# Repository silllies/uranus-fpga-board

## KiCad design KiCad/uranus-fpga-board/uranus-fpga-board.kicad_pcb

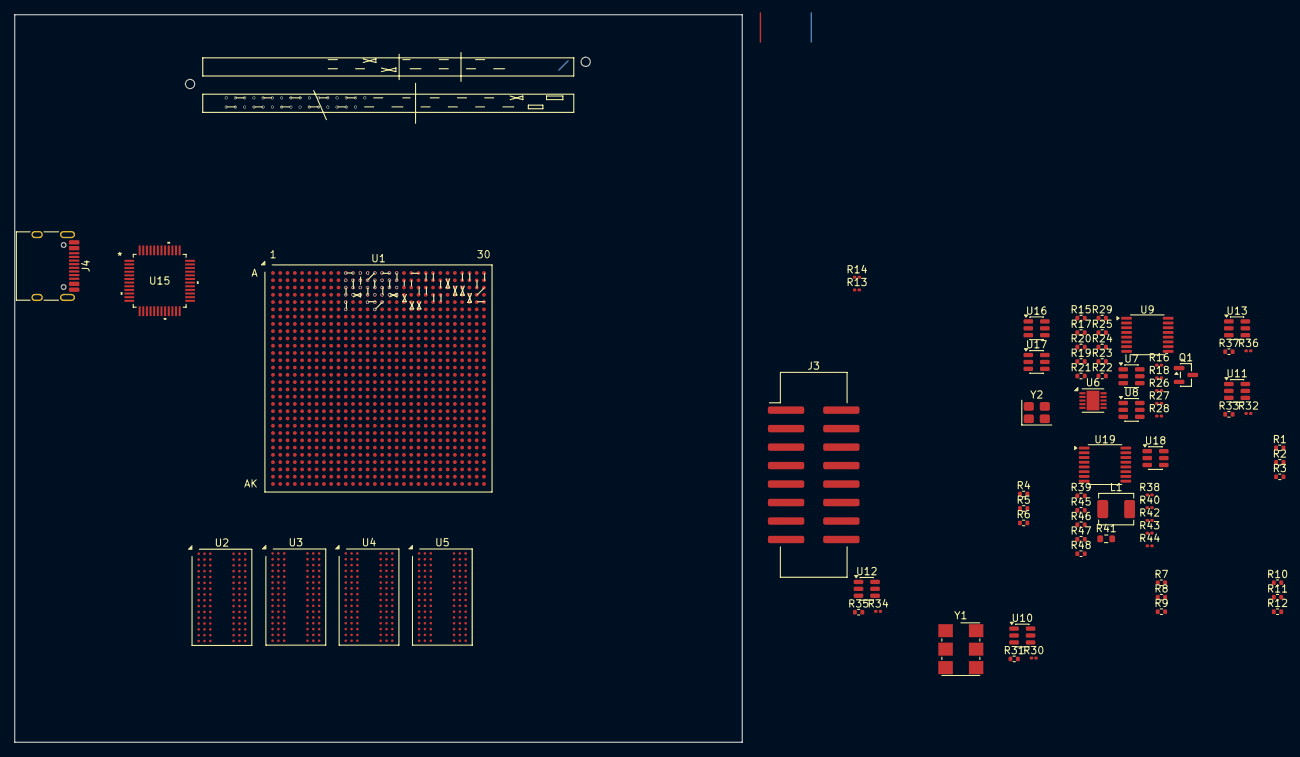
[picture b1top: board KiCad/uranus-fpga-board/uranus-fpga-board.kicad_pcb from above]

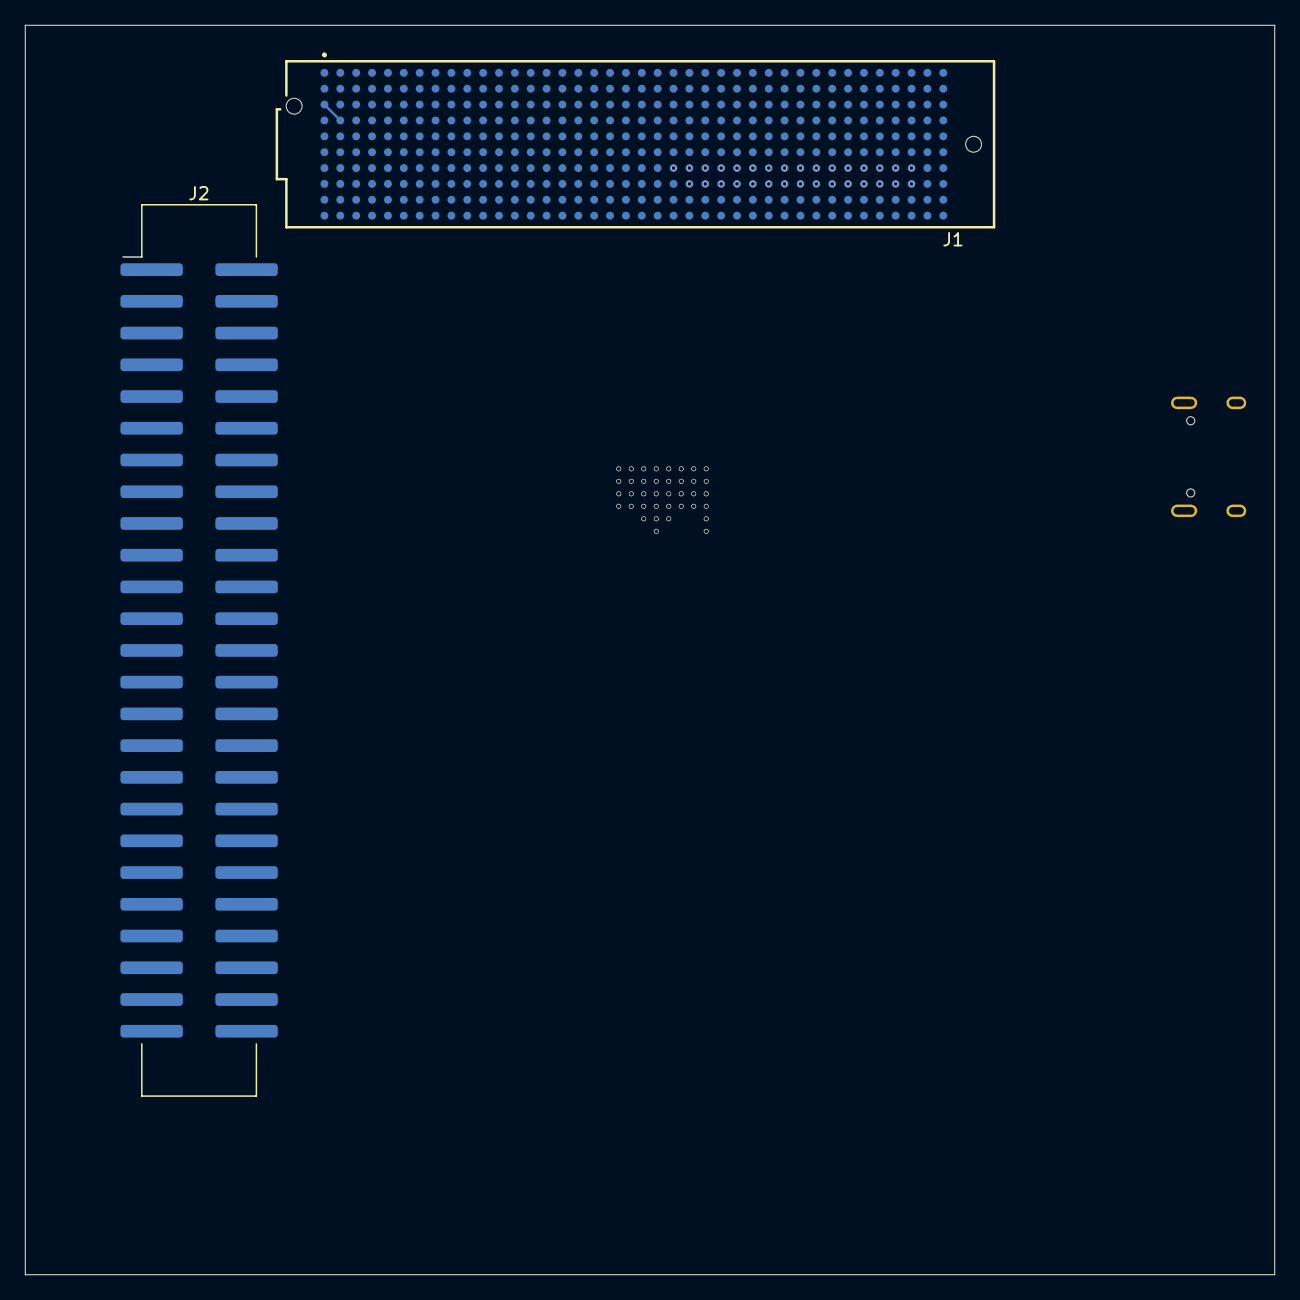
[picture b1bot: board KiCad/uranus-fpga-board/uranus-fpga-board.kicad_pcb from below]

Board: 8 copper layers, 100.0 x 100.0 mm, 74 parts (2 on the bottom side), 244 nets.

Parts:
J1: ASP-134486-01; SAMTEC_ASP-134486-01
J2: 1040100018; IDC-Header_2x25_P2.54mm_Vertical_SMD
J3: IDC 2x8; IDC-Header_2x08_P2.54mm_Vertical_SMD
J4: TYPE-C-31-M-12; USB_C_Receptacle_HRO_TYPE-C-31-M-12
L1: 2.2 μH; L_Chilisin_BMRA00040415
Q1: 2N7002; SOT-23
R1, R2, R4, R5, R7, R8, R10, R11: 1 kΩ; R_0402_1005Metric
R3, R6, R9, R12: 240 Ω; R_0402_1005Metric
R13, R14, R16, R38: 10 kΩ; R_0201_0603Metric
R15: 1.8 kΩ; R_0402_1005Metric
R17: 200 kΩ; R_0402_1005Metric
R18: 7.5 kΩ; R_0201_0603Metric
R19, R20, R22: 57.6 kΩ; R_0402_1005Metric
R21: 232 kΩ; R_0402_1005Metric
R23: 41.2 kΩ; R_0402_1005Metric
R24: 27.4 kΩ; R_0402_1005Metric
R25: 21.5 kΩ; R_0402_1005Metric
R26, R27, R28, R42, R43, R44: 200 kΩ; R_0201_0603Metric
R29: 15.8 kΩ; R_0402_1005Metric
R30, R32, R34, R36: 499 Ω; R_0201_0603Metric
R31, R33, R35, R37: 7.68 kΩ; R_0402_1005Metric
R39: 4.7 kΩ; R_0402_1005Metric
R40: 30 kΩ; R_0201_0603Metric
R41: 8.98 kΩ; R_0603_1608Metric
R45: 13 kΩ; R_0402_1005Metric
R46: 22.1 kΩ; R_0402_1005Metric
R47: 30.9 kΩ; R_0402_1005Metric
R48: 52.3 kΩ; R_0402_1005Metric
U1: XC7K325T-3FFG900E; Xilinx_FFG900_FFG901
U2, U3, U4, U5: NT5CB64M16GP-FL; FBGA-96_8x13mm_Layout9x16_P0.8mm
U6: SY6874DBC; DFN-10-1EP_3x3mm_P0.5mm_EP1.75x2.7mm
U7: TPS2553DBVR; SOT-23-6
U8: SY6288F1ABC; SOT-23-6
U9, U19: TMUX1108; TSSOP-16_4.4x5mm_P0.65mm
U10, U11, U12, U13: TLV6700DDCR; SOT-23-6
U15: FT232HL-REEL; LQFP48_FT232HL_FTD
U16: 93LC56BT; SOT-23-6
U17: USBLC6-2SC6; SOT-23-6
U18: TPS564201DDCR; SOT-23-6
Y1: SX7DF200.000B20F30DNN; Oscillator_SMD_IDT_JU6-6_7.0x5.0mm_P2.54mm
Y2: 3225-12-20-10-10/4B; Crystal_SMD_3225-4Pin_3.2x2.5mm

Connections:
+1V0: U1.M11 (VCCINT), U1.M13 (VCCINT), U1.M15 (VCCINT), U1.M17 (VCCINT), U1.N10 (VCCINT), U1.N12 (VCCINT), U1.N14 (VCCINT), U1.N16 (VCCBRAM), U1.N18 (VCCINT), U1.P11 (VCCINT), U1.P17 (VCCINT), U1.R10 (VCCINT), U1.R12 (VCCINT), U1.R16 (VCCBRAM), U1.R18 (VCCINT), U1.T11 (VCCINT), U1.T17 (VCCINT), U1.U10 (VCCINT), U1.U12 (VCCINT), U1.U16 (VCCBRAM), U1.U18 (VCCINT), U1.V17 (VCCINT), U1.W16 (VCCBRAM), U1.W18 (VCCINT)
+1V5: R1.1, R4.1, R7.1, R10.1, U1.AA9 (VCCO_33), U1.AA19 (VCCO_32), U1.AB16 (VCCO_32), U1.AC3 (VCCO_34), U1.AC13 (VCCO_33), U1.AD10 (VCCO_33), U1.AE7 (VCCO_34), U1.AE17 (VCCO_32), U1.AF4 (VCCO_34), U1.AF14 (VCCO_32), U1.AG1 (VCCO_34), U1.AG11 (VCCO_33), U1.AH8 (VCCO_34), U1.AH18 (VCCO_32), U1.AJ5 (VCCO_34), U1.AJ15 (VCCO_32), U1.AK2 (VCCO_34), U1.AK12 (VCCO_33), U1.Y12 (VCCO_33), U2.A1 (VDDQ), U2.A8 (VDDQ), U2.B2 (VDD), U2.C1 (VDDQ), U2.C9 (VDDQ), U2.D2 (VDDQ), U2.D9 (VDD), U2.E9 (VDDQ), U2.F1 (VDDQ), U2.G7 (VDD), U2.H2 (VDDQ), U2.H9 (VDDQ), U2.K2 (VDD), U2.K8 (VDD), U2.N1 (VDD), U2.N9 (VDD), U2.R1 (VDD), U2.R9 (VDD), U3.A1 (VDDQ), U3.A8 (VDDQ), U3.B2 (VDD), U3.C1 (VDDQ), U3.C9 (VDDQ), U3.D2 (VDDQ), U3.D9 (VDD), U3.E9 (VDDQ), U3.F1 (VDDQ), U3.G7 (VDD), U3.H2 (VDDQ), U3.H9 (VDDQ), U3.K2 (VDD), U3.K8 (VDD), U3.N1 (VDD), U3.N9 (VDD), U3.R1 (VDD), U3.R9 (VDD), U4.A1 (VDDQ), U4.A8 (VDDQ), U4.B2 (VDD), U4.C1 (VDDQ), U4.C9 (VDDQ), U4.D2 (VDDQ), U4.D9 (VDD), U4.E9 (VDDQ), U4.F1 (VDDQ), U4.G7 (VDD), U4.H2 (VDDQ), U4.H9 (VDDQ), U4.K2 (VDD), U4.K8 (VDD), U4.N1 (VDD), U4.N9 (VDD), U4.R1 (VDD), U4.R9 (VDD), U5.A1 (VDDQ), U5.A8 (VDDQ), U5.B2 (VDD), U5.C1 (VDDQ), U5.C9 (VDDQ), U5.D2 (VDDQ), U5.D9 (VDD), U5.E9 (VDDQ), U5.F1 (VDDQ), U5.G7 (VDD), U5.H2 (VDDQ), U5.H9 (VDDQ), U5.K2 (VDD), U5.K8 (VDD), U5.N1 (VDD), U5.N9 (VDD), U5.R1 (VDD), U5.R9 (VDD)
+1V8: U1.P13 (VCCAUX), U1.P15 (VCCADC_0), U1.T13 (VCCAUX), U1.V13 (VCCAUX)
+2V0: U1.V11 (VCCAUX_IO_G0), U1.W10 (VCCAUX_IO_G0), U1.W12 (VCCAUX_IO_G0)
+3V3: J3.1 (VIN), R13.1, R16.1, U1.AB6 (VCCO_0), U1.J25 (VCCO_15), U1.K22 (VCCO_15), U1.L29 (VCCO_15), U1.M26 (VCCO_15), U1.N23 (VCCO_15), U1.P20 (VCCO_15), U1.T9 (VCCO_0), U7.1 (IN), U7.3 (EN), U8.6 (IN), U10.5 (VDD), U11.5 (VDD), U12.5 (VDD), U13.5 (VDD), Y1.6 (VDD)
+3V3AUX: J1.D32 (3P3VAUX), R19.2, U7.6 (OUT)
+3V3_P: J1.C39 (3P3V), J1.D36 (3P3V), J1.D38 (3P3V), J1.D40 (3P3V), R14.1, R20.2, U8.1 (OUT)
+5V0: U9.2 (EN), U9.13 (VDD), U19.2 (EN), U19.13 (VDD)
+12V0: J1.C35 (12P0V), J1.C37 (12P0V), U6.1 (IN), U18.3 (VIN)
+12V0_P: R21.2, U6.8 (OUT), U6.9 (VOUT), U6.10 (VOUT)
/FMC/CLK0_N: J1.H05 (CLK0_M2C_N), U1.B25 (IO_L12N_T1_MRCC_16)
/FMC/CLK0_P: J1.H04 (CLK0_M2C_P), U1.C25 (IO_L12P_T1_MRCC_16)
/FMC/CLK1_N: J1.G03 (CLK1_M2C_N), U1.D28 (IO_L14N_T2_SRCC_16)
/FMC/CLK1_P: J1.G02 (CLK1_M2C_P), U1.E28 (IO_L14P_T2_SRCC_16)
/FMC/DP0_C2M_N: J1.C03 (DP0_C2M_N), U1.B1 (MGTXTXN2_118)
/FMC/DP0_C2M_P: J1.C02 (DP0_C2M_P), U1.B2 (MGTXTXP2_118)
/FMC/DP0_M2C_N: J1.C07 (DP0_M2C_N), U1.B5 (MGTXRXN2_118)
/FMC/DP0_M2C_P: J1.C06 (DP0_M2C_P), U1.B6 (MGTXRXP2_118)
/FMC/GTXCLK0_N: J1.D05 (GBTCLK0_M2C_N), U1.C7 (MGTREFCLK0N_118)
/FMC/GTXCLK0_P: J1.D04 (GBTCLK0_M2C_P), U1.C8 (MGTREFCLK0P_118)
/FMC/LA00_CC_N: J1.G07 (LA00_CC_N), U1.C27 (IO_L13N_T2_MRCC_16)
/FMC/LA00_CC_P: J1.G06 (LA00_CC_P), U1.D27 (IO_L13P_T2_MRCC_16)
/FMC/LA01_N: J1.D09 (LA01_N), U1.E29 (IO_L18P_T2_16)
/FMC/LA01_P: J1.D08 (LA01_P), U1.E30 (IO_L18N_T2_16)
/FMC/LA02_N: J1.H08 (LA02_N), U1.D29 (IO_L16P_T2_16)
/FMC/LA02_P: J1.H07 (LA02_P), U1.C30 (IO_L16N_T2_16)
/FMC/LA03_N: J1.G10 (LA03_N), U1.A30 (IO_L17N_T2_16)
/FMC/LA03_P: J1.G09 (LA03_P), U1.B30 (IO_L17P_T2_16)
/FMC/LA04_N: J1.H11 (LA04_N), U1.B29 (IO_L15N_T2_DQS_16)
/FMC/LA04_P: J1.H10 (LA04_P), U1.C29 (IO_L15P_T2_DQS_16)
/FMC/LA05_N: J1.D12 (LA05_N), U1.D23 (IO_L2N_T0_16)
/FMC/LA05_P: J1.D11 (LA05_P), U1.E23 (IO_L2P_T0_16)
/FMC/LA06_N: J1.C11 (LA06_N), U1.D24 (IO_L4N_T0_16)
/FMC/LA06_P: J1.C10 (LA06_P), U1.E24 (IO_L4P_T0_16)
/FMC/LA07_N: J1.H14 (LA07_N), U1.A27 (IO_L7N_T1_16)
/FMC/LA07_P: J1.H13 (LA07_P), U1.B27 (IO_L7P_T1_16)
/FMC/LA08_N: J1.G13 (LA08_N), U1.A28 (IO_L9N_T1_DQS_16)
/FMC/LA08_P: J1.G12 (LA08_P), U1.B28 (IO_L9P_T1_DQS_16)
/FMC/LA09_N: J1.D15 (LA09_N), U1.C22 (IO_L10N_T1_17)
/FMC/LA09_P: J1.D14 (LA09_P), U1.D22 (IO_L10P_T1_17)
/FMC/LA10_N: J1.C15 (LA10_N), U1.C21 (IO_L8N_T1_17)
/FMC/LA10_P: J1.C14 (LA10_P), U1.D21 (IO_L8P_T1_17)
/FMC/LA11_N: J1.H17 (LA11_N), U1.A23 (IO_L1N_T0_16)
/FMC/LA11_P: J1.H16 (LA11_P), U1.B23 (IO_L1P_T0_16)
/FMC/LA12_N: J1.G16 (LA12_N), U1.B24 (IO_L8N_T1_16)
/FMC/LA12_P: J1.G15 (LA12_P), U1.C24 (IO_L8P_T1_16)
/FMC/LA13_N: J1.D18 (LA13_N), U1.D19 (IO_L14N_T2_SRCC_17)
/FMC/LA13_P: J1.D17 (LA13_P), U1.E19 (IO_L14P_T2_SRCC_17)
/FMC/LA14_N: J1.C19 (LA14_N), U1.C16 (IO_L15N_T2_DQS_17)
/FMC/LA14_P: J1.C18 (LA14_P), U1.D16 (IO_L15P_T2_DQS_17)
/FMC/LA15_N: J1.H20 (LA15_N), U1.A20 (IO_L21P_T3_DQS_17)
/FMC/LA15_P: J1.H19 (LA15_P), U1.A21 (IO_L21N_T3_DQS_17)
/FMC/LA16_N: J1.G19 (LA16_N), U1.A22 (IO_L23N_T3_17)
/FMC/LA16_P: J1.G18 (LA16_P), U1.B22 (IO_L23P_T3_17)
/FMC/LA17_CC_N: J1.D21 (LA17_CC_N), U1.D13 (IO_L13N_T2_MRCC_18)
/FMC/LA17_CC_P: J1.D20 (LA17_CC_P), U1.D12 (IO_L13P_T2_MRCC_18)
/FMC/LA18_CC_N: J1.C23 (LA18_CC_N), U1.D18 (IO_L13N_T2_MRCC_17)
/FMC/LA18_CC_P: J1.C22 (LA18_CC_P), U1.D17 (IO_L13P_T2_MRCC_17)
/FMC/LA19_N: J1.H23 (LA19_N), U1.C19 (IO_L24P_T3_17)
/FMC/LA19_P: J1.H22 (LA19_P), U1.B19 (IO_L24N_T3_17)
/FMC/LA20_N: J1.G22 (LA20_N), U1.C20 (IO_L19P_T3_17)
/FMC/LA20_P: J1.G21 (LA20_P), U1.B20 (IO_L19N_T3_VREF_17)
/FMC/LA21_N: J1.H26 (LA21_N), U1.C17 (IO_L17P_T2_17)
/FMC/LA21_P: J1.H25 (LA21_P), U1.B17 (IO_L17N_T2_17)
/FMC/LA22_N: J1.G25 (LA22_N), U1.B18 (IO_L22P_T3_17)
/FMC/LA22_P: J1.G24 (LA22_P), U1.A18 (IO_L22N_T3_17)
/FMC/LA23_N: J1.D24 (LA23_N), U1.F15 (IO_L19P_T3_18)
/FMC/LA23_P: J1.D23 (LA23_P), U1.E16 (IO_L19N_T3_VREF_18)
/FMC/LA24_N: J1.H29 (LA24_N), U1.C15 (IO_L23P_T3_18)
/FMC/LA24_P: J1.H28 (LA24_P), U1.B15 (IO_L23N_T3_18)
/FMC/LA25_N: J1.G28 (LA25_N), U1.A16 (IO_L20P_T3_17)
/FMC/LA25_P: J1.G27 (LA25_P), U1.A17 (IO_L20N_T3_17)
/FMC/LA26_N: J1.D27 (LA26_N), U1.E11 (IO_L16N_T2_18)
/FMC/LA26_P: J1.D26 (LA26_P), U1.F11 (IO_L16P_T2_18)
/FMC/LA27_N: J1.C27 (LA27_N), U1.E14 (IO_L20P_T3_18)
/FMC/LA27_P: J1.C26 (LA27_P), U1.E15 (IO_L20N_T3_18)
/FMC/LA28_N: J1.H32 (LA28_N), U1.D14 (IO_L21P_T3_DQS_18)
/FMC/LA28_P: J1.H31 (LA28_P), U1.C14 (IO_L21N_T3_DQS_18)
/FMC/LA29_N: J1.G31 (LA29_N), U1.B14 (IO_L24P_T3_18)
/FMC/LA29_P: J1.G30 (LA29_P), U1.A15 (IO_L24N_T3_18)
/FMC/LA30_N: J1.H35 (LA30_N), U1.A11 (IO_L17P_T2_18)
/FMC/LA30_P: J1.H34 (LA30_P), U1.A12 (IO_L17N_T2_18)
/FMC/LA31_N: J1.G34 (LA31_N), U1.B13 (IO_L22P_T3_18)
/FMC/LA31_P: J1.G33 (LA31_P), U1.A13 (IO_L22N_T3_18)
/FMC/LA32_N: J1.H38 (LA32_N), U1.D11 (IO_L18P_T2_18)
/FMC/LA32_P: J1.H37 (LA32_P), U1.C11 (IO_L18N_T2_18)
/FMC/LA33_N: J1.G37 (LA33_N), U1.C12 (IO_L15P_T2_DQS_18)
/FMC/LA33_P: J1.G36 (LA33_P), U1.B12 (IO_L15N_T2_DQS_18)
/FMC/PG: J1.D01 (PG_C2M), R14.2, U10.1 (OUTA), U10.6 (OUTB), U11.1 (OUTA), U11.6 (OUTB), U12.1 (OUTA), U12.6 (OUTB), U13.1 (OUTA), U13.6 (OUTB)
/FMC/Power Management/PRSNT: Q1.3 (D), R16.2, U6.2 (VIN), U6.3 (VIN), U6.7 (EN), U8.4 (EN)
/FMC/Power Management/Window Comparator +3V3AUX/IN: R19.1, R30.1, U10.3 (INA+)
/FMC/Power Management/Window Comparator +3V3_P/IN: R20.1, R34.1, U12.3 (INA+)
/FMC/Power Management/Window Comparator +12V0_P/IN: R21.1, R32.1, U11.3 (INA+)
/FMC/Power Management/Window Comparator VADJ/IN: R36.1, U9.8 (D), U13.3 (INA+)
/FMC/Power Management/~PRSNT: J1.H02 (~PRSNT_M2C), Q1.1 (G), R13.2
/FMC/REG_EN: R38.1, U18.5 (EN)
/FMC/SEL_A0: R26.2, R42.1, U9.1 (A0), U19.1 (A0)
/FMC/SEL_A1: R27.2, R43.1, U9.16 (A1), U19.16 (A1)
/FMC/SEL_A2: R28.2, R44.1, U9.15 (A2), U19.15 (A2)
/FPGA/CKE: U1.AJ9 (IO_L15P_T2_DQS_33), U2.K9 (CKE), U3.K9 (CKE), U4.K9 (CKE), U5.K9 (CKE)
/FPGA/H0.DM: U1.AF3 (IO_L7P_T1_34), U2.D3 (UDM)
/FPGA/H0.DQ0: U1.AF2 (IO_L7N_T1_34), U2.D7 (DQ8)
/FPGA/H0.DQ1: U1.AE1 (IO_L8P_T1_34), U2.C3 (DQ9)
/FPGA/H0.DQ2: U1.AF1 (IO_L8N_T1_34), U2.C8 (DQ10)
/FPGA/H0.DQ3: U1.AE4 (IO_L10P_T1_34), U2.C2 (DQ11)
/FPGA/H0.DQ4: U1.AE3 (IO_L10N_T1_34), U2.A7 (DQ12)
/FPGA/H0.DQ5: U1.AE5 (IO_L11P_T1_SRCC_34), U2.A2 (DQ13)
/FPGA/H0.DQ6: U1.AF5 (IO_L11N_T1_SRCC_34), U2.B8 (DQ14)
/FPGA/H0.DQ7: U1.AF6 (IO_L12P_T1_MRCC_34), U2.A3 (DQ15)
/FPGA/H0.DQS_N: U1.AG3 (IO_L9N_T1_DQS_34), U2.B7 (~UDQS)
/FPGA/H0.DQS_P: U1.AG4 (IO_L9P_T1_DQS_34), U2.C7 (UDQS)
/FPGA/H1.DM: U1.AF8 (IO_L19P_T3_34), U3.D3 (UDM)
/FPGA/H1.DQ0: U1.AF7 (IO_L20P_T3_34), U3.D7 (DQ8)
/FPGA/H1.DQ1: U1.AG7 (IO_L20N_T3_34), U3.C3 (DQ9)
/FPGA/H1.DQ2: U1.AJ6 (IO_L22P_T3_34), U3.C8 (DQ10)
/FPGA/H1.DQ3: U1.AK6 (IO_L22N_T3_34), U3.C2 (DQ11)
/FPGA/H1.DQ4: U1.AJ8 (IO_L23P_T3_34), U3.A7 (DQ12)
/FPGA/H1.DQ5: U1.AK8 (IO_L23N_T3_34), U3.A2 (DQ13)
/FPGA/H1.DQ6: U1.AK5 (IO_L24P_T3_34), U3.B8 (DQ14)
/FPGA/H1.DQ7: U1.AK4 (IO_L24N_T3_34), U3.A3 (DQ15)
/FPGA/H1.DQS_N: U1.AJ7 (IO_L21N_T3_DQS_34), U3.B7 (~UDQS)
/FPGA/H1.DQS_P: U1.AH7 (IO_L21P_T3_DQS_34), U3.C7 (UDQS)
/FPGA/H2.DM: U1.AJ19 (IO_L7P_T1_32), U4.D3 (UDM)
/FPGA/H2.DQ0: U1.AK19 (IO_L7N_T1_32), U4.D7 (DQ8)
/FPGA/H2.DQ1: U1.AG19 (IO_L8P_T1_32), U4.C3 (DQ9)
/FPGA/H2.DQ2: U1.AH19 (IO_L8N_T1_32), U4.C8 (DQ10)
/FPGA/H2.DQ3: U1.AD19 (IO_L10P_T1_32), U4.C2 (DQ11)
/FPGA/H2.DQ4: U1.AE19 (IO_L10N_T1_32), U4.A7 (DQ12)
/FPGA/H2.DQ5: U1.AF18 (IO_L11P_T1_SRCC_32), U4.A2 (DQ13)
/FPGA/H2.DQ6: U1.AG18 (IO_L11N_T1_SRCC_32), U4.B8 (DQ14)
/FPGA/H2.DQ7: U1.AF17 (IO_L12P_T1_MRCC_32), U4.A3 (DQ15)
/FPGA/H2.DQS_N: U1.AK18 (IO_L9N_T1_DQS_32), U4.B7 (~UDQS)
/FPGA/H2.DQS_P: U1.AJ18 (IO_L9P_T1_DQS_32), U4.C7 (UDQS)
/FPGA/H3.DM: U1.AA18 (IO_L16P_T2_32), U5.D3 (UDM)
/FPGA/H3.DQ0: U1.AD18 (IO_L13P_T2_MRCC_32), U5.D7 (DQ8)
/FPGA/H3.DQ1: U1.AE18 (IO_L13N_T2_MRCC_32), U5.C3 (DQ9)
/FPGA/H3.DQ2: U1.AD17 (IO_L14P_T2_SRCC_32), U5.C8 (DQ10)
/FPGA/H3.DQ3: U1.AD16 (IO_L14N_T2_SRCC_32), U5.C2 (DQ11)
/FPGA/H3.DQ4: U1.AB18 (IO_L16N_T2_32), U5.A7 (DQ12)
/FPGA/H3.DQ5: U1.AB19 (IO_L17P_T2_32), U5.A2 (DQ13)
/FPGA/H3.DQ6: U1.AC19 (IO_L17N_T2_32), U5.B8 (DQ14)
/FPGA/H3.DQ7: U1.AB17 (IO_L18P_T2_32), U5.A3 (DQ15)
/FPGA/H3.DQS_N: U1.Y18 (IO_L15N_T2_DQS_32), U5.B7 (~UDQS)
/FPGA/H3.DQS_P: U1.Y19 (IO_L15P_T2_DQS_32), U5.C7 (UDQS)
/FPGA/L0.DM: U1.AD4 (IO_L1P_T0_34), U2.E7 (LDM)
/FPGA/L0.DQ0: U1.AD3 (IO_L1N_T0_34), U2.E3 (DQ0)
/FPGA/L0.DQ1: U1.AC2 (IO_L2P_T0_34), U2.F7 (DQ1)
/FPGA/L0.DQ2: U1.AC1 (IO_L2N_T0_34), U2.F2 (DQ2)
/FPGA/L0.DQ3: U1.AC5 (IO_L4P_T0_34), U2.F8 (DQ3)
/FPGA/L0.DQ4: U1.AC4 (IO_L4N_T0_34), U2.H3 (DQ4)
/FPGA/L0.DQ5: U1.AD6 (IO_L5P_T0_34), U2.H8 (DQ5)
/FPGA/L0.DQ6: U1.AE6 (IO_L5N_T0_34), U2.G2 (DQ6)
/FPGA/L0.DQ7: U1.AC7 (IO_L6P_T0_34), U2.H7 (DQ7)
/FPGA/L0.DQS_N: U1.AD1 (IO_L3N_T0_DQS_34), U2.G3 (~LDQS)
/FPGA/L0.DQS_P: U1.AD2 (IO_L3P_T0_DQS_34), U2.F3 (LDQS)
/FPGA/L1.DM: U1.AH2 (IO_L16P_T2_34), U3.E7 (LDM)
/FPGA/L1.DQ0: U1.AH4 (IO_L13P_T2_MRCC_34), U3.E3 (DQ0)
/FPGA/L1.DQ1: U1.AJ4 (IO_L13N_T2_MRCC_34), U3.F7 (DQ1)
/FPGA/L1.DQ2: U1.AH6 (IO_L14P_T2_SRCC_34), U3.F2 (DQ2)
/FPGA/L1.DQ3: U1.AH5 (IO_L14N_T2_SRCC_34), U3.F8 (DQ3)
/FPGA/L1.DQ4: U1.AJ2 (IO_L16N_T2_34), U3.H3 (DQ4)
/FPGA/L1.DQ5: U1.AJ1 (IO_L17P_T2_34), U3.H8 (DQ5)
/FPGA/L1.DQ6: U1.AK1 (IO_L17N_T2_34), U3.G2 (DQ6)
/FPGA/L1.DQ7: U1.AJ3 (IO_L18P_T2_34), U3.H7 (DQ7)
/FPGA/L1.DQS_N: U1.AH1 (IO_L15N_T2_DQS_34), U3.G3 (~LDQS)
/FPGA/L1.DQS_P: U1.AG2 (IO_L15P_T2_DQS_34), U3.F3 (LDQS)
/FPGA/L2.DM: U1.AK16 (IO_L1P_T0_32), U4.E7 (LDM)
/FPGA/L2.DQ0: U1.AK15 (IO_L1N_T0_32), U4.E3 (DQ0)
/FPGA/L2.DQ1: U1.AG15 (IO_L2P_T0_32), U4.F7 (DQ1)
/FPGA/L2.DQ2: U1.AH15 (IO_L2N_T0_32), U4.F2 (DQ2)
/FPGA/L2.DQ3: U1.AF15 (IO_L4P_T0_32), U4.F8 (DQ3)
/FPGA/L2.DQ4: U1.AG14 (IO_L4N_T0_32), U4.H3 (DQ4)
/FPGA/L2.DQ5: U1.AH17 (IO_L5P_T0_32), U4.H8 (DQ5)
/FPGA/L2.DQ6: U1.AJ17 (IO_L5N_T0_32), U4.G2 (DQ6)
/FPGA/L2.DQ7: U1.AE16 (IO_L6P_T0_32), U4.H7 (DQ7)
/FPGA/L2.DQS_N: U1.AJ16 (IO_L3N_T0_DQS_32), U4.G3 (~LDQS)
/FPGA/L2.DQS_P: U1.AH16 (IO_L3P_T0_DQS_32), U4.F3 (LDQS)
/FPGA/L3.DM: U1.AE15 (IO_L19P_T3_32), U5.E7 (LDM)
/FPGA/L3.DQ0: U1.AA15 (IO_L20P_T3_32), U5.E3 (DQ0)
/FPGA/L3.DQ1: U1.AB15 (IO_L20N_T3_32), U5.F7 (DQ1)
/FPGA/L3.DQ2: U1.AC14 (IO_L22P_T3_32), U5.F2 (DQ2)
/FPGA/L3.DQ3: U1.AD14 (IO_L22N_T3_32), U5.F8 (DQ3)
/FPGA/L3.DQ4: U1.AA17 (IO_L23P_T3_32), U5.H3 (DQ4)
/FPGA/L3.DQ5: U1.AA16 (IO_L23N_T3_32), U5.H8 (DQ5)
/FPGA/L3.DQ6: U1.Y16 (IO_L24P_T3_32), U5.G2 (DQ6)
/FPGA/L3.DQ7: U1.Y15 (IO_L24N_T3_32), U5.H7 (DQ7)
/FPGA/L3.DQS_N: U1.AC15 (IO_L21N_T3_DQS_32), U5.G3 (~LDQS)
/FPGA/L3.DQS_P: U1.AC16 (IO_L21P_T3_DQS_32), U5.F3 (LDQS)
/FPGA/ODT: U1.AK9 (IO_L15N_T2_DQS_33), U2.K1 (ODT), U3.K1 (ODT), U4.K1 (ODT), U5.K1 (ODT)
/FPGA/~CAS: U1.AE9 (IO_L10N_T1_33), U2.K3 (~CAS), U3.K3 (~CAS), U4.K3 (~CAS), U5.K3 (~CAS)
/FPGA/~CS: U1.AF11 (IO_L11N_T1_SRCC_33), U2.L2 (~CS), U3.L2 (~CS), U4.L2 (~CS), U5.L2 (~CS)
/FPGA/~RAS: U1.AD9 (IO_L10P_T1_33), U2.J3 (~RAS), U3.J3 (~RAS), U4.J3 (~RAS), U5.J3 (~RAS)
/FPGA/~RESET: U1.AD11 (IO_L12N_T1_MRCC_33), U2.T2 (~RESET), U3.T2 (~RESET), U4.T2 (~RESET), U5.T2 (~RESET)
/FPGA/~WE: U1.AE11 (IO_L11P_T1_SRCC_33), U2.L3 (~WE), U3.L3 (~WE), U4.L3 (~WE), U5.L3 (~WE)
/Power/VADJ/MUX_1V2: R48.1, U19.5 (S2)
/Power/VADJ/MUX_1V5: R47.1, U19.6 (S3)
/Power/VADJ/MUX_1V8: R46.1, U19.7 (S4)
/Power/VADJ/MUX_2V5: R45.1, U19.12 (S5)
/Power/VADJ/MUX_3V3: R41.1, U19.11 (S6)
/Power/VADJ/VFB: R40.2, U18.4 (VFB), U19.8 (D)
/RAM/A0: U1.AD8 (IO_L8P_T1_33), U2.N3 (A0), U3.N3 (A0), U4.N3 (A0), U5.N3 (A0)
/RAM/A1: U1.AC10 (IO_L7N_T1_33), U2.P7 (A1), U3.P7 (A1), U4.P7 (A1), U5.P7 (A1)
/RAM/A2: U1.AB10 (IO_L7P_T1_33), U2.P3 (A2), U3.P3 (A2), U4.P3 (A2), U5.P3 (A2)
/RAM/A3: U1.AB13 (IO_L6N_T0_VREF_33), U2.N2 (A3), U3.N2 (A3), U4.N2 (A3), U5.N2 (A3)
/RAM/A4: U1.AA13 (IO_L6P_T0_33), U2.P8 (A4), U3.P8 (A4), U4.P8 (A4), U5.P8 (A4)
/RAM/A5: U1.AA10 (IO_L5N_T0_33), U2.P2 (A5), U3.P2 (A5), U4.P2 (A5), U5.P2 (A5)
/RAM/A6: U1.AA11 (IO_L5P_T0_33), U2.R8 (A6), U3.R8 (A6), U4.R8 (A6), U5.R8 (A6)
/RAM/A7: U1.Y10 (IO_L4N_T0_33), U2.R2 (A7), U3.R2 (A7), U4.R2 (A7), U5.R2 (A7)
/RAM/A8: U1.Y11 (IO_L4P_T0_33), U2.T8 (A8), U3.T8 (A8), U4.T8 (A8), U5.T8 (A8)
/RAM/A9: U1.AB8 (IO_L2N_T0_33), U2.R3 (A9), U3.R3 (A9), U4.R3 (A9), U5.R3 (A9)
/RAM/A10: U1.AA8 (IO_L2P_T0_33), U2.L7 (A10/AP), U3.L7 (A10/AP), U4.L7 (A10/AP), U5.L7 (A10/AP)
/RAM/A11: U1.AB12 (IO_L1N_T0_33), U2.R7 (A11), U3.R7 (A11), U4.R7 (A11), U5.R7 (A11)
/RAM/A12: U1.AA12 (IO_L1P_T0_33), U2.N7 (A12/~BC), U3.N7 (A12/~BC), U4.N7 (A12/~BC), U5.N7 (A12/~BC)
/RAM/BA0: U1.AC11 (IO_L9N_T1_DQS_33), U2.M2 (BA0), U3.M2 (BA0), U4.M2 (BA0), U5.M2 (BA0)
/RAM/BA1: U1.AC12 (IO_L9P_T1_DQS_33), U2.N8 (BA1), U3.N8 (BA1), U4.N8 (BA1), U5.N8 (BA1)
/RAM/BA2: U1.AE8 (IO_L8N_T1_33), U2.M3 (BA2), U3.M3 (BA2), U4.M3 (BA2), U5.M3 (BA2)
/RAM/CK_N: U1.AC9 (IO_L3N_T0_DQS_33), U2.K7 (~CK), U3.K7 (~CK), U4.K7 (~CK), U5.K7 (~CK)
/RAM/CK_P: U1.AB9 (IO_L3P_T0_DQS_33), U2.J7 (CK), U3.J7 (CK), U4.J7 (CK), U5.J7 (CK)
GND: J1.C01 (GND), J1.C04 (GND), J1.C05 (GND), J1.C08 (GND), J1.C09 (GND), J1.C12 (GND), J1.C13 (GND), J1.C16 (GND), J1.C17 (GND), J1.C20 (GND), J1.C21 (GND), J1.C24 (GND), J1.C25 (GND), J1.C28 (GND), J1.C29 (GND), J1.C32 (GND), J1.C33 (GND), J1.C34 (GA0), J1.C36 (GND), J1.C38 (GND), J1.C40 (GND), J1.D02 (GND), J1.D03 (GND), J1.D06 (GND), J1.D07 (GND), J1.D10 (GND), J1.D13 (GND), J1.D16 (GND), J1.D19 (GND), J1.D22 (GND), J1.D25 (GND), J1.D28 (GND), J1.D35 (GA1), J1.D37 (GND), J1.D39 (GND), J1.G01 (GND), J1.G04 (GND), J1.G05 (GND), J1.G08 (GND), J1.G11 (GND), J1.G14 (GND), J1.G17 (GND), J1.G20 (GND), J1.G23 (GND), J1.G26 (GND), J1.G29 (GND), J1.G32 (GND), J1.G35 (GND), J1.G38 (GND), J1.G40 (GND), J1.H03 (GND), J1.H06 (GND), J1.H09 (GND), J1.H12 (GND), J1.H15 (GND), J1.H18 (GND), J1.H21 (GND), J1.H24 (GND), J1.H27 (GND), J1.H30 (GND), J1.H33 (GND), J1.H36 (GND), J1.H39 (GND), J2.1 (GND), J2.2 (GND), J2.17 (GND), J2.18 (GND), J2.33 (GND), J2.34 (GND), J2.37 (GND), J2.38 (GND), J2.41 (GND), J2.42 (GND), J2.45 (GND), J2.46 (GND), J2.49 (GND), J2.50 (GND), J3.2 (GND), J3.3 (GND), J3.6 (GND), J3.7 (GND), J3.10 (GND), J3.11 (GND), J3.14 (GND), J3.15 (GND), Q1.2 (S), R2.2, R3.2, R5.2, R6.2, R8.2, R9.2, R11.2, R12.2, R15.2, R17.2, R18.2, R26.1, R27.1, R28.1, R31.2, R33.2, R35.2, R37.2, R38.2, R39.2, R41.2, R42.2, R43.2, R44.2, R45.2, R46.2, R47.2, R48.2, U1.A1 (GND), U1.A2 (GND), U1.A5 (GND), U1.A6 (GND), U1.A9 (GND), U1.A14 (GND), U1.A24 (GND), U1.AA1 (GND), U1.AA2 (GND), U1.AA5 (GND), U1.AA6 (GND), U1.AA7 (GND), U1.AA14 (GND), U1.AA24 (GND), U1.AB3 (GND), U1.AB4 (GND), U1.AB11 (GND), U1.AB21 (GND), U1.AC8 (GND), U1.AC18 (GND), U1.AC28 (GND), U1.AD5 (GND), U1.AD15 (GND), U1.AD25 (GND), U1.AE2 (GND), U1.AE12 (GND), U1.AE22 (GND), U1.AF9 (GND), U1.AF19 (GND), U1.AF29 (GND), U1.AG6 (GND), U1.AG16 (GND), U1.AG26 (GND), U1.AH3 (GND), U1.AH13 (GND), U1.AH23 (GND), U1.AJ10 (GND), U1.AJ20 (GND), U1.AJ30 (GND), U1.AK7 (GND), U1.AK17 (GND), U1.AK27 (GND), U1.B4 (GND), U1.B8 (GND), U1.B9 (GND), U1.B11 (GND), U1.B21 (GND), U1.C1 (GND), U1.C2 (GND), U1.C6 (GND), U1.C9 (GND), U1.C10 (VCCBATT_0), U1.C18 (GND), U1.C28 (GND), U1.D4 (GND), U1.D8 (GND), U1.D9 (GND), U1.D15 (GND), U1.D25 (GND), U1.E1 (GND), U1.E2 (GND), U1.E6 (GND), U1.E9 (GND), U1.E12 (GND), U1.E22 (GND), U1.F4 (GND), U1.F8 (GND), U1.F9 (GND), U1.F19 (GND), U1.F29 (GND), U1.G1 (GND), U1.G2 (GND), U1.G6 (GND), U1.G9 (GND), U1.G16 (GND), U1.G26 (GND), U1.H4 (GND), U1.H8 (GND), U1.H9 (GND), U1.H13 (GND), U1.H23 (GND), U1.J1 (GND), U1.J2 (GND), U1.J6 (GND), U1.J9 (GND), U1.J10 (GND), U1.J20 (GND), U1.J30 (GND), U1.K4 (GND), U1.K8 (GND), U1.K9 (GND), U1.K17 (GND), U1.K27 (GND), U1.L1 (GND), U1.L2 (GND), U1.L6 (GND), U1.L9 (GND), U1.L14 (GND), U1.L24 (GND), U1.M4 (GND), U1.M8 (GND), U1.M9 (GND), U1.M12 (GND), U1.M14 (GND), U1.M16 (GND), U1.M18 (GND), U1.M21 (GND), U1.N1 (GND), U1.N2 (GND), U1.N6 (GND), U1.N9 (GND), U1.N11 (GND), U1.N13 (GND), U1.N15 (GND), U1.N17 (GND), U1.N28 (GND), U1.P4 (GND), U1.P8 (GND), U1.P9 (GND), U1.P10 (GND), U1.P12 (GND), U1.P14 (GNDADC_0), U1.P16 (GND), U1.P18 (GND), U1.P25 (GND), U1.R1 (GND), U1.R2 (GND), U1.R6 (GND), U1.R9 (GND), U1.R11 (GND), U1.R13 (GND), U1.R17 (GND), U1.R22 (GND), U1.T4 (GND), U1.T8 (GND), U1.T10 (GND), U1.T12 (GND), U1.T16 (GND), U1.T18 (GND), U1.T19 (GND), U1.T29 (GND), U1.U1 (GND), U1.U2 (GND), U1.U6 (GND), U1.U9 (GND), U1.U11 (GND), U1.U13 (GND), U1.U17 (GND), U1.U26 (GND), U1.V4 (GND), U1.V8 (GND), U1.V9 (GND), U1.V10 (GND), U1.V12 (GND), U1.V14 (GND), U1.V16 (GND), U1.V18 (GND), U1.V23 (GND), U1.W1 (GND), U1.W2 (GND), U1.W6 (GND), U1.W9 (GND), U1.W11 (GND), U1.W13 (GND), U1.W15 (GND), U1.W17 (GND), U1.W20 (GND), U1.W30 (GND), U1.Y3 (GND), U1.Y4 (GND), U1.Y7 (GND), U1.Y8 (GND), U1.Y9 (GND), U1.Y17 (GND), U1.Y27 (GND), U2.A9 (VSS), U2.B1 (VSSQ), U2.B3 (VSS), U2.B9 (VSSQ), U2.D1 (VSSQ), U2.D8 (VSSQ), U2.E1 (VSS), U2.E2 (VSSQ), U2.E8 (VSSQ), U2.F9 (VSSQ), U2.G1 (VSSQ), U2.G8 (VSS), U2.G9 (VSSQ), U2.J2 (VSS), U2.J8 (VSS), U2.M1 (VSS), U2.M9 (VSS), U2.P1 (VSS), U2.P9 (VSS), U2.T1 (VSS), U2.T9 (VSS), U3.A9 (VSS), U3.B1 (VSSQ), U3.B3 (VSS), U3.B9 (VSSQ), U3.D1 (VSSQ), U3.D8 (VSSQ), U3.E1 (VSS), U3.E2 (VSSQ), U3.E8 (VSSQ), U3.F9 (VSSQ), U3.G1 (VSSQ), U3.G8 (VSS), U3.G9 (VSSQ), U3.J2 (VSS), U3.J8 (VSS), U3.M1 (VSS), U3.M9 (VSS), U3.P1 (VSS), U3.P9 (VSS), U3.T1 (VSS), U3.T9 (VSS), U4.A9 (VSS), U4.B1 (VSSQ), U4.B3 (VSS), U4.B9 (VSSQ), U4.D1 (VSSQ), U4.D8 (VSSQ), U4.E1 (VSS), U4.E2 (VSSQ), U4.E8 (VSSQ), U4.F9 (VSSQ), U4.G1 (VSSQ), U4.G8 (VSS), U4.G9 (VSSQ), U4.J2 (VSS), U4.J8 (VSS), U4.M1 (VSS), U4.M9 (VSS), U4.P1 (VSS), U4.P9 (VSS), U4.T1 (VSS), U4.T9 (VSS), U5.A9 (VSS), U5.B1 (VSSQ), U5.B3 (VSS), U5.B9 (VSSQ), U5.D1 (VSSQ), U5.D8 (VSSQ), U5.E1 (VSS), U5.E2 (VSSQ), U5.E8 (VSSQ), U5.F9 (VSSQ), U5.G1 (VSSQ), U5.G8 (VSS), U5.G9 (VSSQ), U5.J2 (VSS), U5.J8 (VSS), U5.M1 (VSS), U5.M9 (VSS), U5.P1 (VSS), U5.P9 (VSS), U5.T1 (VSS), U5.T9 (VSS), U6.11 (GND), U7.2 (GND), U8.2 (GND), U9.3 (VSS), U9.14 (GND), U10.2 (GND), U11.2 (GND), U12.2 (GND), U13.2 (GND), U18.1 (GND), U19.3 (VSS), U19.14 (GND), Y1.3 (GND), Y2.2 (GND_2)
unnamed: J4.A1 (GND), J4.A12 (GND), J4.B1 (GND), J4.B12 (GND)
unnamed: J4.A4 (VBUS), J4.A9 (VBUS), J4.B4 (VBUS), J4.B9 (VBUS)
unnamed: U1.V15 (VCCAUX), U1.W14 (VCCAUX)
unnamed: R1.2, R2.1, U2.H1 (VREFDQ), U2.M8 (VREFCA)
unnamed: R3.1, U2.L8 (ZQ)
unnamed: R4.2, R5.1, U3.H1 (VREFDQ), U3.M8 (VREFCA)
unnamed: R6.1, U3.L8 (ZQ)
unnamed: R7.2, R8.1, U4.H1 (VREFDQ), U4.M8 (VREFCA)
unnamed: R9.1, U4.L8 (ZQ)
unnamed: R10.2, R11.1, U5.H1 (VREFDQ), U5.M8 (VREFCA)
unnamed: R12.1, U5.L8 (ZQ)
unnamed: R18.1, U6.5 (ILIM)
unnamed: R17.1, U7.5 (ILIM)
unnamed: R15.1, U8.5 (ILIM)
unnamed: R29.1, U9.5 (S2)
unnamed: R25.1, U9.6 (S3)
unnamed: R24.1, U9.7 (S4)
unnamed: R23.1, U9.12 (S5)
unnamed: R22.1, U9.11 (S6)
unnamed: R30.2, R31.1, U10.4 (INB-)
unnamed: R32.2, R33.1, U11.4 (INB-)
unnamed: R34.2, R35.1, U12.4 (INB-)
unnamed: R36.2, R37.1, U13.4 (INB-)
unnamed: L1.1, U18.2 (SW)
VADJ: J1.G39 (VADJ), J1.H40 (VADJ), L1.2, R22.2, R23.2, R24.2, R25.2, R29.2, R39.1, R40.1, U1.A19 (VCCO_17), U1.A29 (VCCO_16), U1.B16 (VCCO_17), U1.B26 (VCCO_16), U1.C13 (VCCO_18), U1.C23 (VCCO_16), U1.D10 (VCCO_18), U1.D20 (VCCO_17), U1.D30 (VCCO_16), U1.E17 (VCCO_17), U1.E27 (VCCO_16), U1.F14 (VCCO_18), U1.F24 (VCCO_16), U1.G11 (VCCO_18), U1.G21 (VCCO_17), U1.H18 (VCCO_17), U1.H28 (VCCO_16), U1.J15 (VCCO_18), U1.K12 (VCCO_18), U1.L19 (VCCO_17)

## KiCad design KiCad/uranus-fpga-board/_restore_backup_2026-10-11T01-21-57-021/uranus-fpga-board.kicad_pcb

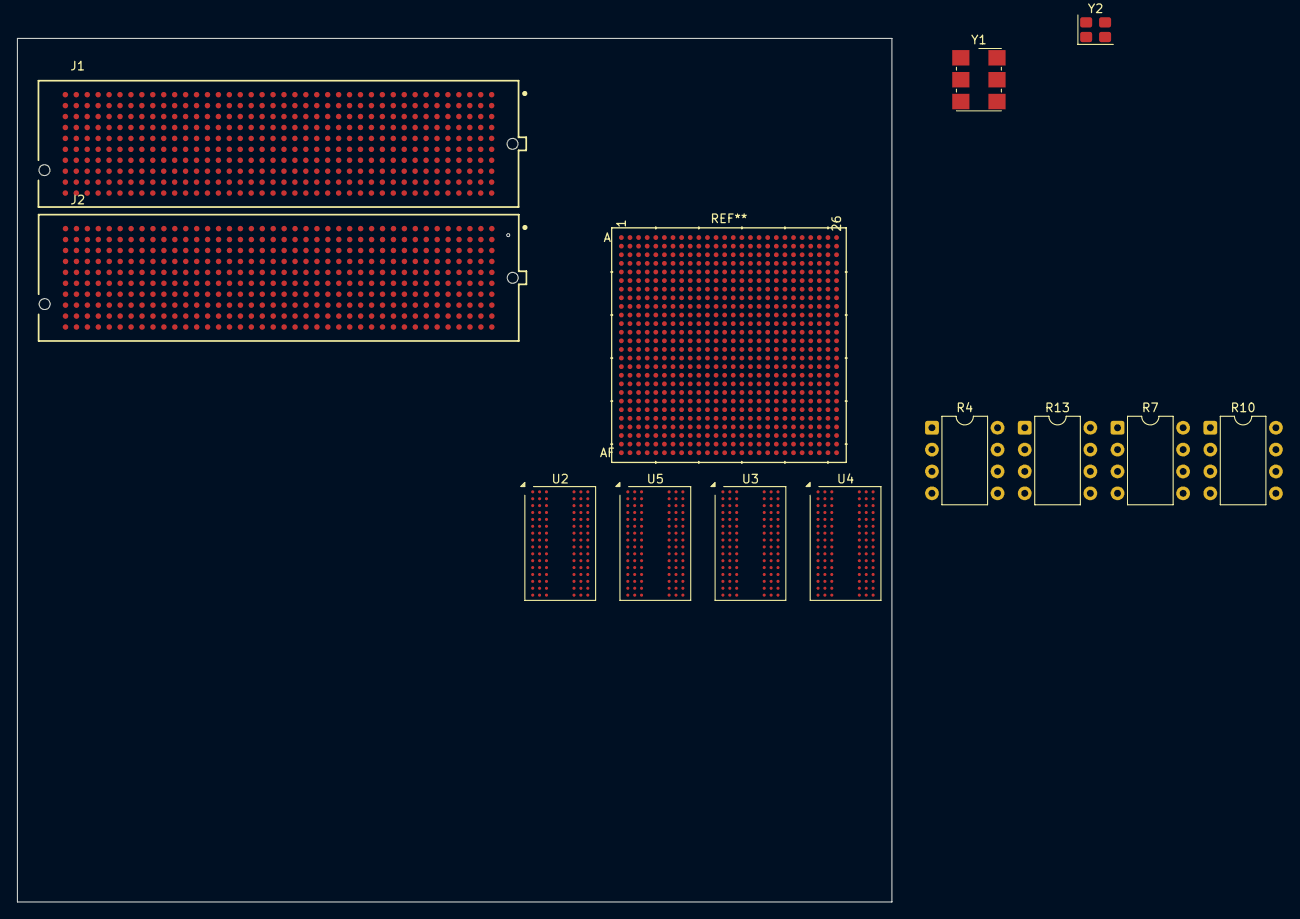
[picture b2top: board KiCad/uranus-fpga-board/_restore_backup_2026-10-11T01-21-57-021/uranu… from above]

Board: 8 copper layers, 101.6 x 100.3 mm, 12 parts (0 on the bottom side), 34 nets, no tracks yet.

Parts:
J1, J2: ASP-134488-01; SAMTEC_ASP-134488-01
R4, R7, R10, R13: 240Ω; DIP-8_W7.62mm
U2, U3, U4, U5: AS4C256M16D3; FBGA-96_8x13mm_Layout9x16_P0.8mm
Y1: SX7DF200.000B20F30DNN; Oscillator_SMD_IDT_JU6-6_7.0x5.0mm_P2.54mm
Y2: ASE-xxxMHz; Crystal_SMD_3225-4Pin_3.2x2.5mm

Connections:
+1V5: U2.A1 (VDDQ), U2.A8 (VDDQ), U2.B2 (VDD), U2.C1 (VDDQ), U2.C9 (VDDQ), U2.D2 (VDDQ), U2.D9 (VDD), U2.E9 (VDDQ), U2.F1 (VDDQ), U2.G7 (VDD), U2.H2 (VDDQ), U2.H9 (VDDQ), U2.K2 (VDD), U2.K8 (VDD), U2.N1 (VDD), U2.N9 (VDD), U2.R1 (VDD), U2.R9 (VDD), U3.A1 (VDDQ), U3.A8 (VDDQ), U3.B2 (VDD), U3.C1 (VDDQ), U3.C9 (VDDQ), U3.D2 (VDDQ), U3.D9 (VDD), U3.E9 (VDDQ), U3.F1 (VDDQ), U3.G7 (VDD), U3.H2 (VDDQ), U3.H9 (VDDQ), U3.K2 (VDD), U3.K8 (VDD), U3.N1 (VDD), U3.N9 (VDD), U3.R1 (VDD), U3.R9 (VDD), U4.A1 (VDDQ), U4.A8 (VDDQ), U4.B2 (VDD), U4.C1 (VDDQ), U4.C9 (VDDQ), U4.D2 (VDDQ), U4.D9 (VDD), U4.E9 (VDDQ), U4.F1 (VDDQ), U4.G7 (VDD), U4.H2 (VDDQ), U4.H9 (VDDQ), U4.K2 (VDD), U4.K8 (VDD), U4.N1 (VDD), U4.N9 (VDD), U4.R1 (VDD), U4.R9 (VDD), U5.A1 (VDDQ), U5.A8 (VDDQ), U5.B2 (VDD), U5.C1 (VDDQ), U5.C9 (VDDQ), U5.D2 (VDDQ), U5.D9 (VDD), U5.E9 (VDDQ), U5.F1 (VDDQ), U5.G7 (VDD), U5.H2 (VDDQ), U5.H9 (VDDQ), U5.K2 (VDD), U5.K8 (VDD), U5.N1 (VDD), U5.N9 (VDD), U5.R1 (VDD), U5.R9 (VDD)
A0: U2.N3 (A0), U3.N3 (A0), U4.N3 (A0), U5.N3 (A0)
A1: U2.P7 (A1), U3.P7 (A1), U4.P7 (A1), U5.P7 (A1)
A2: U2.P3 (A2), U3.P3 (A2), U4.P3 (A2), U5.P3 (A2)
A3: U2.N2 (A3), U3.N2 (A3), U4.N2 (A3), U5.N2 (A3)
A4: U2.P8 (A4), U3.P8 (A4), U4.P8 (A4), U5.P8 (A4)
A5: U2.P2 (A5), U3.P2 (A5), U4.P2 (A5), U5.P2 (A5)
A6: U2.R8 (A6), U3.R8 (A6), U4.R8 (A6), U5.R8 (A6)
A7: U2.R2 (A7), U3.R2 (A7), U4.R2 (A7), U5.R2 (A7)
A8: U2.T8 (A8), U3.T8 (A8), U4.T8 (A8), U5.T8 (A8)
A9: U2.R3 (A9), U3.R3 (A9), U4.R3 (A9), U5.R3 (A9)
A10: U2.L7 (A10/AP), U3.L7 (A10/AP), U4.L7 (A10/AP), U5.L7 (A10/AP)
A11: U2.R7 (A11), U3.R7 (A11), U4.R7 (A11), U5.R7 (A11)
A12: U2.N7 (A12/~BC), U3.N7 (A12/~BC), U4.N7 (A12/~BC), U5.N7 (A12/~BC)
BA0: U2.M2 (BA0), U3.M2 (BA0), U4.M2 (BA0), U5.M2 (BA0)
BA1: U2.N8 (BA1), U3.N8 (BA1), U4.N8 (BA1), U5.N8 (BA1)
BA2: U2.M3 (BA2), U3.M3 (BA2), U4.M3 (BA2), U5.M3 (BA2)
CAS: U2.K3 (~CAS), U3.K3 (~CAS), U4.K3 (~CAS), U5.K3 (~CAS)
CKE: U2.K9 (CKE), U3.K9 (CKE), U4.K9 (CKE), U5.K9 (CKE)
CK_N: U2.K7 (~CK), U3.K7 (~CK), U4.K7 (~CK), U5.K7 (~CK)
CK_P: U2.J7 (CK), U3.J7 (CK), U4.J7 (CK), U5.J7 (CK)
CS: U2.L2 (~CS), U3.L2 (~CS), U4.L2 (~CS), U5.L2 (~CS)
GND: R4.1, R7.1, R10.1, R13.1, U2.A9 (VSS), U2.B1 (VSSQ), U2.B3 (VSS), U2.B9 (VSSQ), U2.D1 (VSSQ), U2.D8 (VSSQ), U2.E1 (VSS), U2.E2 (VSSQ), U2.E8 (VSSQ), U2.F9 (VSSQ), U2.G1 (VSSQ), U2.G8 (VSS), U2.G9 (VSSQ), U2.J2 (VSS), U2.J8 (VSS), U2.M1 (VSS), U2.M9 (VSS), U2.P1 (VSS), U2.P9 (VSS), U2.T1 (VSS), U2.T9 (VSS), U3.A9 (VSS), U3.B1 (VSSQ), U3.B3 (VSS), U3.B9 (VSSQ), U3.D1 (VSSQ), U3.D8 (VSSQ), U3.E1 (VSS), U3.E2 (VSSQ), U3.E8 (VSSQ), U3.F9 (VSSQ), U3.G1 (VSSQ), U3.G8 (VSS), U3.G9 (VSSQ), U3.J2 (VSS), U3.J8 (VSS), U3.M1 (VSS), U3.M9 (VSS), U3.P1 (VSS), U3.P9 (VSS), U3.T1 (VSS), U3.T9 (VSS), U4.A9 (VSS), U4.B1 (VSSQ), U4.B3 (VSS), U4.B9 (VSSQ), U4.D1 (VSSQ), U4.D8 (VSSQ), U4.E1 (VSS), U4.E2 (VSSQ), U4.E8 (VSSQ), U4.F9 (VSSQ), U4.G1 (VSSQ), U4.G8 (VSS), U4.G9 (VSSQ), U4.J2 (VSS), U4.J8 (VSS), U4.M1 (VSS), U4.M9 (VSS), U4.P1 (VSS), U4.P9 (VSS), U4.T1 (VSS), U4.T9 (VSS), U5.A9 (VSS), U5.B1 (VSSQ), U5.B3 (VSS), U5.B9 (VSSQ), U5.D1 (VSSQ), U5.D8 (VSSQ), U5.E1 (VSS), U5.E2 (VSSQ), U5.E8 (VSSQ), U5.F9 (VSSQ), U5.G1 (VSSQ), U5.G8 (VSS), U5.G9 (VSSQ), U5.J2 (VSS), U5.J8 (VSS), U5.M1 (VSS), U5.M9 (VSS), U5.P1 (VSS), U5.P9 (VSS), U5.T1 (VSS), U5.T9 (VSS), Y1.3 (GND)
unnamed: R4.2, U2.L8 (ZQ)
unnamed: R7.2, U3.L8 (ZQ)
unnamed: R10.2, U4.L8 (ZQ)
unnamed: R13.2, U5.L8 (ZQ)
ODT: U2.K1 (ODT), U3.K1 (ODT), U4.K1 (ODT), U5.K1 (ODT)
RAS: U2.J3 (~RAS), U3.J3 (~RAS), U4.J3 (~RAS), U5.J3 (~RAS)
RESET: U2.T2 (~RESET), U3.T2 (~RESET), U4.T2 (~RESET), U5.T2 (~RESET)
VREF_0: U2.H1 (VREFDQ), U2.M8 (VREFCA), U5.H1 (VREFDQ), U5.M8 (VREFCA)
VREF_1: U3.H1 (VREFDQ), U3.M8 (VREFCA)
VREF_2: U4.H1 (VREFDQ), U4.M8 (VREFCA)
WE: U2.L3 (~WE), U3.L3 (~WE), U4.L3 (~WE), U5.L3 (~WE)
